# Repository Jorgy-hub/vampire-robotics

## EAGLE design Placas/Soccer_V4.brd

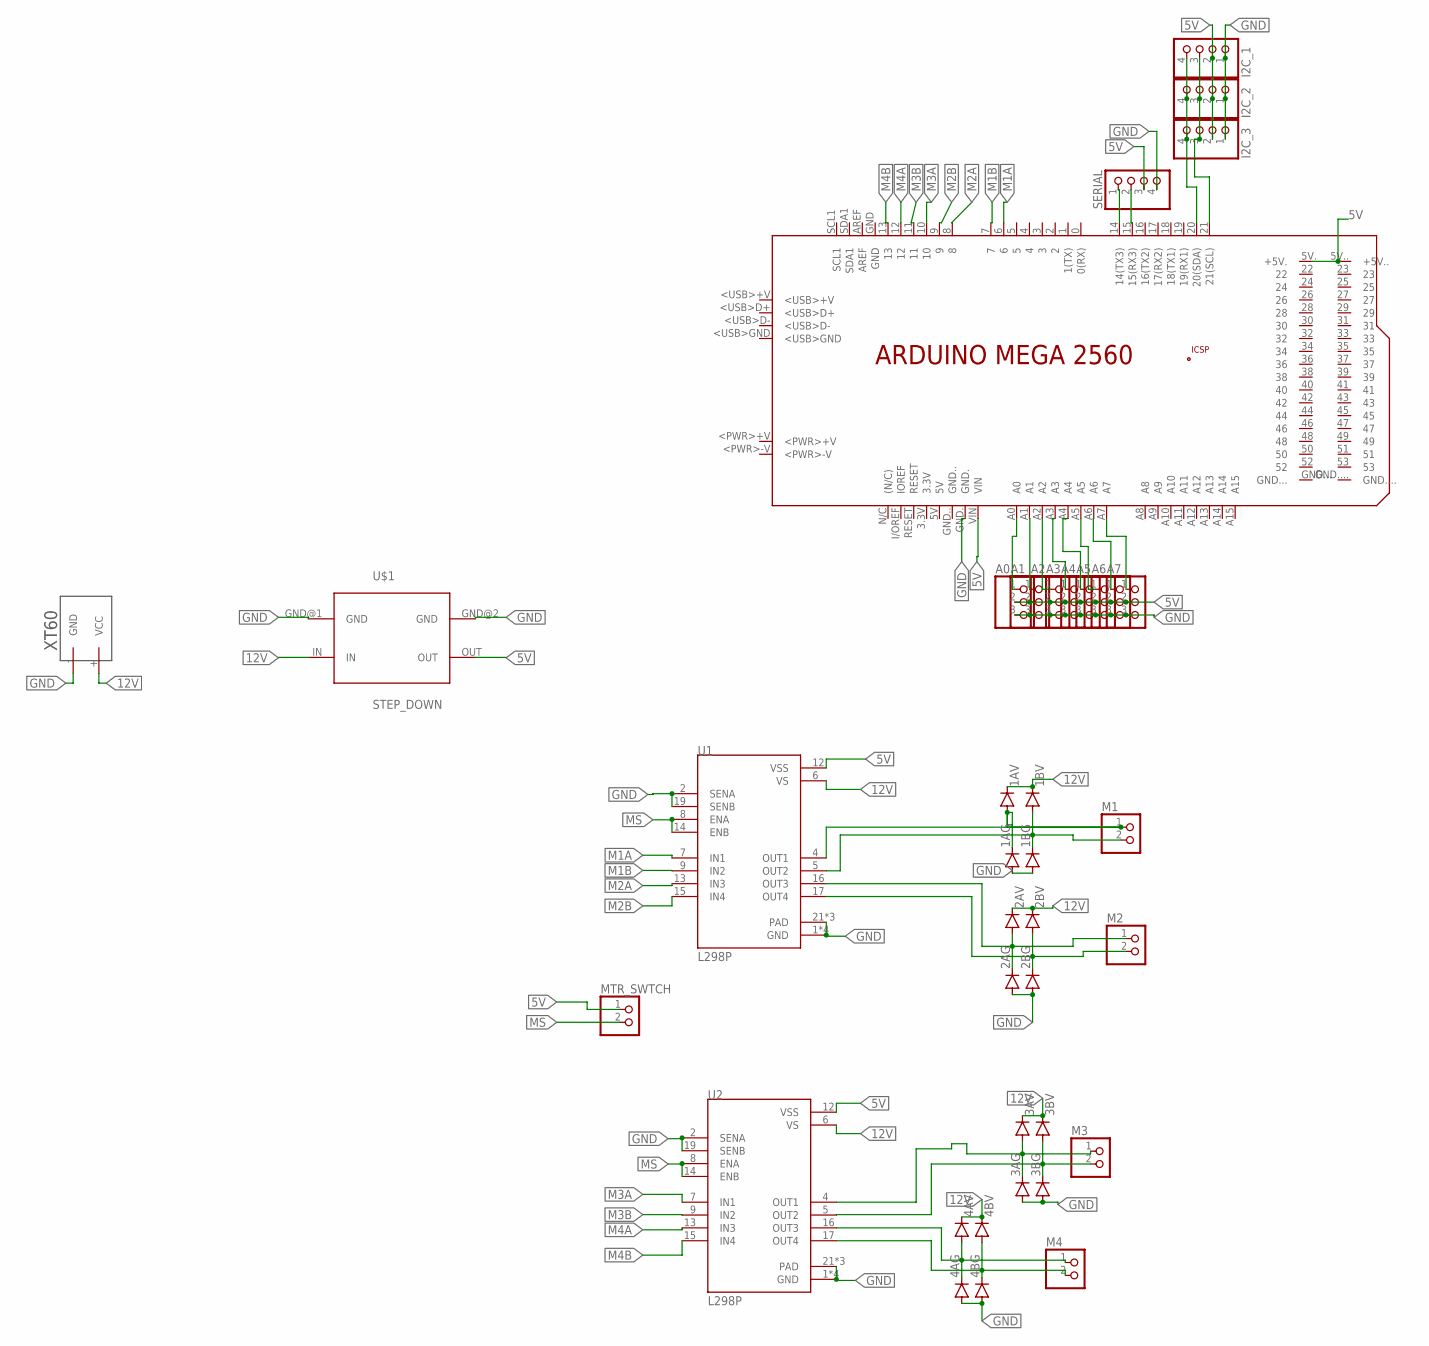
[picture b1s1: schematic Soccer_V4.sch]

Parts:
1AG, 1AV, 1BG, 1BV, 2AG, 2AV, 2BG, 2BV, 3AG, 3AV, 3BG, 3BV, 4AG, 4AV, 4BG, 4BV: 1N4004; DO41-10
A0, A1, A2, A3, A4, A5, A6, A7: PINHD-1X3; 1X03
I2C_1, I2C_2, I2C_3: PINHD-1X4; 1X04
M1, M2, M3, M4: PINHD-1X2; 1X02
MTR_SWTCH: PINHD-1X2; 1X02
PCB1: ARDUINO_MEGA2560
SERIAL: PINHD-1X4; 1X04
U1, U2: L298P; SOIC127P1420X360-20N
U$1: STEP_DOWN; STEP_DOWN_5V
U$2: XT60

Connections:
5V: A0.2, A1.2, A2.2, A3.2, A4.2, A5.2, A6.2, A7.2, I2C_1.2, I2C_2.2, I2C_3.2, MTR_SWTCH.1, PCB1.5V. (+5V.), PCB1.5V.. (+5V..), PCB1.VIN, SERIAL.3, U1.12 (VSS), U2.12 (VSS), U$1.OUT
12V: 1AV.C, 1BV.C, 2AV.C, 2BV.C, 3AV.C, 3BV.C, 4AV.C, 4BV.C, U1.6 (VS), U2.6 (VS), U$1.IN, U$2.+ (VCC)
GND: 1AG.A, 1BG.A, 2AG.A, 2BG.A, 3AG.A, 3BG.A, 4AG.A, 4BG.A, A0.3, A1.3, A2.3, A3.3, A4.3, A5.3, A6.3, A7.3, I2C_1.1, I2C_2.1, I2C_3.1, PCB1.GND., SERIAL.4, U1.1 (GND), U1.2 (SENA), U1.10 (GND), U1.11 (GND), U1.19 (SENB), U1.20 (GND), U1.21 (PAD), U1.22 (PAD), U1.23 (PAD), U2.1 (GND), U2.2 (SENA), U2.10 (GND), U2.11 (GND), U2.19 (SENB), U2.20 (GND), U2.21 (PAD), U2.22 (PAD), U2.23 (PAD), U$1.GND@1 (GND), U$1.GND@2 (GND), U$2.- (GND)
M1A: PCB1.6, U1.7 (IN1)
M1B: PCB1.7, U1.9 (IN2)
M2A: PCB1.8, U1.13 (IN3)
M2B: PCB1.9, U1.15 (IN4)
M3A: PCB1.10, U2.7 (IN1)
M3B: PCB1.11, U2.9 (IN2)
M4A: PCB1.12, U2.13 (IN3)
M4B: PCB1.13, U2.15 (IN4)
MS: MTR_SWTCH.2, U1.8 (ENA), U1.14 (ENB), U2.8 (ENA), U2.14 (ENB)
unnamed: A0.1, PCB1.A0
unnamed: A1.1, PCB1.A1
unnamed: A2.1, PCB1.A2
unnamed: A3.1, PCB1.A3
unnamed: A4.1, PCB1.A4
unnamed: A5.1, PCB1.A5
unnamed: A6.1, PCB1.A6
unnamed: A7.1, PCB1.A7
unnamed: PCB1.14 (14(TX3)), SERIAL.1
unnamed: PCB1.15 (15(RX3)), SERIAL.2
unnamed: I2C_1.4, I2C_2.4, I2C_3.4, PCB1.20 (20(SDA))
unnamed: I2C_1.3, I2C_2.3, I2C_3.3, PCB1.21 (21(SCL))
unnamed: 1AG.C, 1AV.A, M1.1, U1.4 (OUT1)
unnamed: 1BG.C, 1BV.A, M1.2, U1.5 (OUT2)
unnamed: 2AG.C, 2AV.A, M2.1, U1.16 (OUT3)
unnamed: 2BG.C, 2BV.A, M2.2, U1.17 (OUT4)
unnamed: 3AG.C, 3AV.A, M3.1, U2.4 (OUT1)
unnamed: 3BG.C, 3BV.A, M3.2, U2.5 (OUT2)
unnamed: 4AG.C, 4AV.A, M4.1, U2.16 (OUT3)
unnamed: 4BG.C, 4BV.A, M4.2, U2.17 (OUT4)

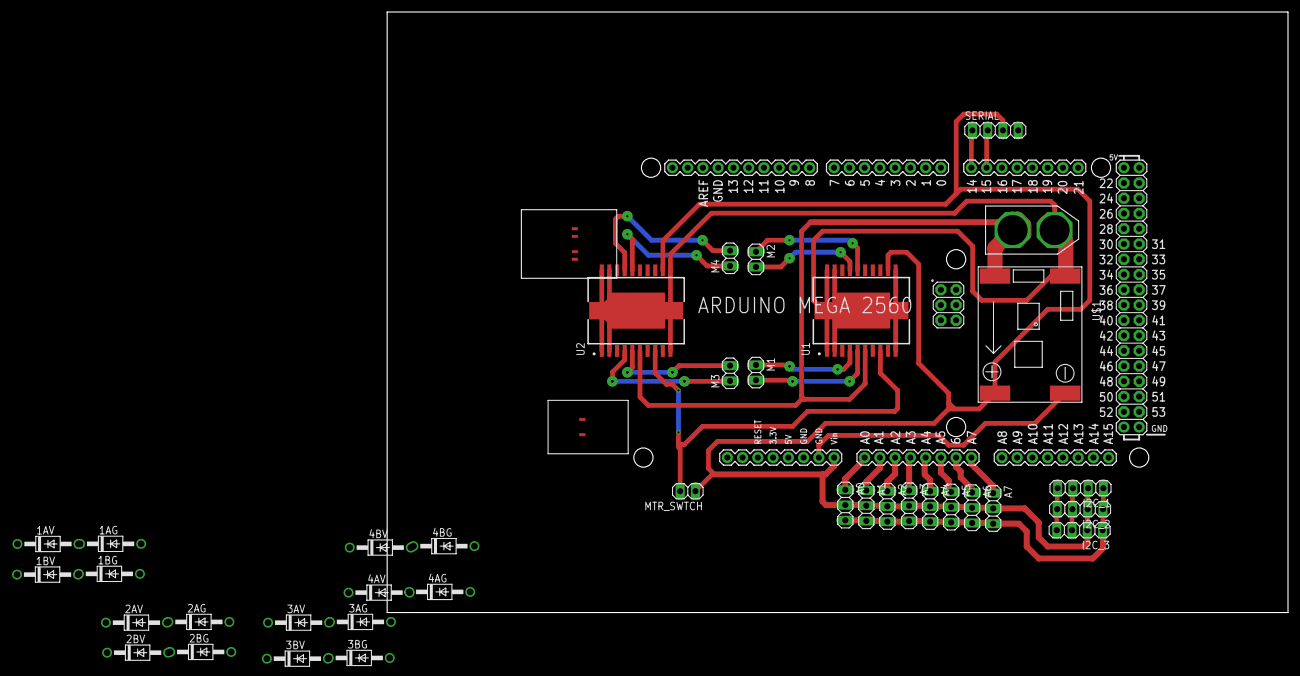
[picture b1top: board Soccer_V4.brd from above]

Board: 2 copper layers, 150.0 x 100.0 mm, 38 parts (0 on the bottom side), 32 nets.
